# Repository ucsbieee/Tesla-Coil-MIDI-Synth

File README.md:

# UCSB IEEE Tesla Coil MIDI Synthesizer

This is the firmware and design files for a device to convert MIDI data to pulses to drive a Tesla coil. It enumerates as a USB MIDI device and can be sent live play data or a recorded MIDI file. It also enumerates as a USB audio device and can be sent PCM audio for greater control or for live instrument use.

The circuit board is based off of the [Arduino Due](https://docs.arduino.cc/hardware/due). It uses the similar SAM3A4C MCU, and has a fiber optic output for the big DRSSTC and a BNC port for the small Tesla Coil. It also has isolated physical MIDI in/out ports for connecting other instruments or daisy-chaining more MIDI interrupters. See [ucsbieee/ArduinoCore-SAM3A4C](https://github.com/ucsbieee/ArduinoCore-SAM3A4C) for an Arduino IDE board definition.

The device has six voices, which can each produce a single square wave tone at a variable duty cycle. They are ORed together to give a polyphonic effect.

## Uploading Firmware

New firmware can be uploaded using the Arduino IDE and the aforementioned [board definition](https://github.com/ucsbieee/ArduinoCore-SAM3A4C), or the [latest release](https://github.com/ucsbieee/Tesla-Coil-MIDI-Synth/releases/latest) (`.bin` file) can be uploaded using [BOSSA](https://github.com/shumatech/BOSSA) ([available from Homebrew](https://formulae.brew.sh/formula/bossa)).

### Arduino Library Dependencies
Available from the Arduino IDE library manager
 * [MIDIUSB](https://github.com/arduino-libraries/MIDIUSB)
 * [DueFlashStorage](https://github.com/sebnil/DueFlashStorage) (only if `SAVE_BASE_MIDI` is enabled, which it is not by default)

## Emulator

There is also an emulator that can be compiled to run on a normal computer so that songs can be developed without the physical hardware.

## MIDI Information

### MIDI Channels
 1. Clean (no effects)
 2. Effects
 3. Arpeggio and effects
 4. Drums

Standard MIDI pitch bend and aftertouch messages apply to all channels.

### Effects (CC number in parentheses)
 * Tremolo (rate = 102, depth = 92, delay = 103)
 * Vibrato (rate = 76, depth = 77, delay = 78)
 * ADSR (116, 117, 118, 119)
 * Arpeggio rate (14)

### Drum Samples
 * Kick (36/C2)
 * Snare (40/E2)
 * Clap (39/D#2)
 * Tom (48/C3)
 * Closed hi-hat (42/F#2)

### Physical MIDI Ports
All MIDI messages that come in over USB or the MIDI IN port are sent out the MIDI OUT port. Additionally, all messages that come in over the MIDI IN port are sent back to the computer over USB. This allows daisy-chaining multiple controllers using the physical MIDI ports, and allows recording any inputs from the physical MIDI IN port to the computer. Be careful not to create infinite MIDI loops in your DAW because of these behaviors.

## Audio Processing Modes
 * **Predictive**: Predict how much energy will be in a pulse based on the filtered derivative near zero crossing.
 * **Pulse Energy**: Output a pulse after a delay (~5ms) with width proportional to the area of the input pulse above the noise gate level. Pulse width clamped to maximum setting.
 * **Schmitt**: Output on when audio exceeds the noise gate level, then only turn off again once audio falls below negative noise gate level (Schmitt trigger behavior). Pulse width clamped to maximum setting.
 * **Clamped Binary**: Output on when audio exceeds the noise gate level. Pulse width clamped to maximum setting.
 * **Binary**: Output on when audio exceeds the noise gate level.
 * **Binary DDT**: Output on when the derivative of the audio exceeds a certain threshold. Pulse width clamped to maximum setting.
 * **Bin Oct Down**: Toggle output on rising edge. Input schmitt triggered. Output pulse width limited.
 * **PWM**: Output 48kHz PWM with pulse width proportional to the sample value. Audio baseline level subtracted away.
 * **PWM DDT**: Output 48kHz PWM with pulse width proportional to the derivative of the audio.

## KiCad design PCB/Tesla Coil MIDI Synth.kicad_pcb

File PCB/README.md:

# PCB

## Audio

We had the idea of using sampled audio output after the V2 boards were made. Unfortunately, the (unused) pins that have the necessary DMA capability are not broken out on the board. So, to get audio capability, you will need to solder a very thin wire (~34AWG) underneath the D10 pad on the microcontroller and run it to EXT_IN on the expansion header. Hope you're comfortable with BGA soldering :)

## Hacking
There are twelve extra pins on the board marked "Expansion," and they're there so you can add extra inputs or whatever you want to the board. Three are power (5V, 3.3V, GND), and seven go to digital/ADC pins on the MCU. The Arduino board definition is based off of the DUE, so take a look at the [DUE schematic](https://www.arduino.cc/en/uploads/Main/arduino-Due-schematic.pdf) or [variant.cpp](https://github.com/ucsbieee/ArduinoCore-SAM3A4C/blob/master/variants/arduino_due_x/variant.cpp) to see which Arduino pins they map to. These could be good for adding physical controls/music input of some kind.

There's also an input that is ORed with the voice signals before being sent to the outputs, and a 3.3V logic level copy of that combined output signal available. You can use these to make use of the output circuitry to control the Tesla coil with your own signals, combine voices from multiple interrupter boards (chaos), or whatever else you can think of.

## Erase and Reset Buttons
Pressing the "Erase" button on the PCB immediately deletes the firmware. Don't push it unless you intend to. This microcontroller has the SAM-BA bootloader included in ROM which is activated when the chip is blank, causing it to enumerate as a USB serial device and accept new firmware. If you ever get the board into a state where you can't program it, hit the erase button then reset and that should fix it. After uploading new firmware to a blank chip, you may need to re-power (instead of reset) the board. If it wasn't blank, you usually can just hit the reset button to make it run the new firmware.

If you accidentally nuked the chip, there's a firmware binary file in this repo and you can upload it using [bossa](https://github.com/shumatech/BOSSA/releases).

## If you want to make more

There should be a few extra unpopulated boards in the lab somewhere. See [BOM.csv](https://github.com/ucsbieee/Tesla-Coil-MIDI-Synth/blob/master/PCB/BOM.csv) for a list of parts you'll need. Parts without a DigiKey part number are generic stuff. Most resistors and caps are 0603, with a few 0805 (see footprint column).

You'll also likely want to use a solder paste stencil, especially for the BGA microcontroller. A file for the stencil is in the Gerber folder.

If you guys ever build a Tesla Coil symphony with a bunch of these things, please invite me back, I want to see :)

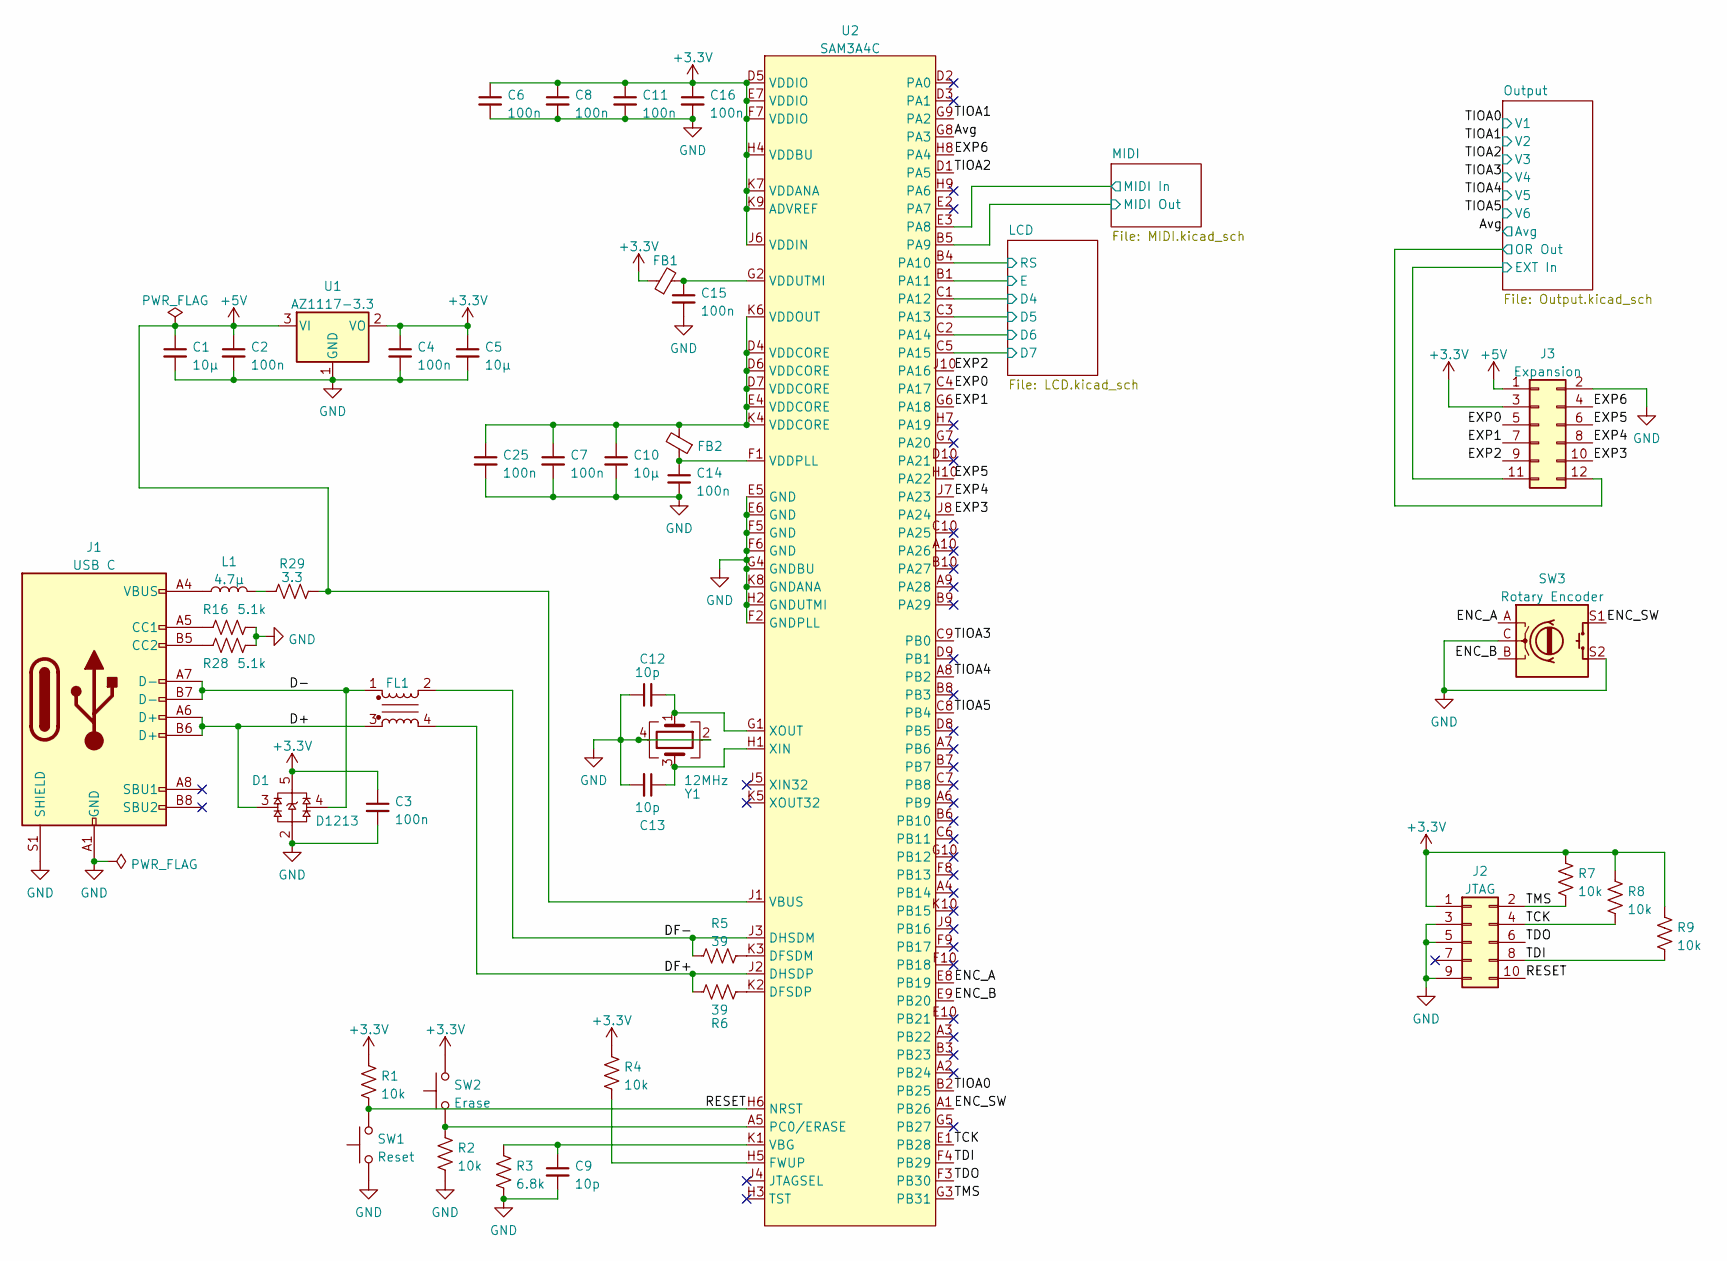
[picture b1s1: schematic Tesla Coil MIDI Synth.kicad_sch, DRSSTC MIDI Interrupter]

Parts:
C1, C5, C10: 10µ; C_0805_2012Metric_Pad1.18x1.45mm_HandSolder
C2, C3, C4, C6, C7, C8, C11, C14, C15, C16, C25: 100n; C_0603_1608Metric_Pad1.08x0.95mm_HandSolder
C9, C12, C13: 10p; C_0603_1608Metric_Pad1.08x0.95mm_HandSolder
D1: D1213; SOT25
FB1, FB2: FerriteBead_Small; L_0805_2012Metric_Pad1.05x1.20mm_HandSolder
FL1: Filter_EMI_CommonMode; Bourns_SRF2012AA
J1: USB C; GCT_USBC_USB4105
J2: JTAG; PinHeader_2x05_P1.27mm_Vertical
J3: Expansion; PinHeader_2x06_P2.54mm_Vertical
L1: 4.7µ; L_0805_2012Metric_Pad1.05x1.20mm_HandSolder
R1, R2, R4, R7, R8, R9: 10k; R_0603_1608Metric_Pad0.98x0.95mm_HandSolder
R3: 6.8k; R_0603_1608Metric_Pad0.98x0.95mm_HandSolder
R5, R6: 39; R_0603_1608Metric_Pad0.98x0.95mm_HandSolder
R16, R28: 5.1k; R_0603_1608Metric_Pad0.98x0.95mm_HandSolder
R29: 3.3; R_0603_1608Metric_Pad0.98x0.95mm_HandSolder
SW1: Reset; SW_PUSH_6mm
SW2: Erase; SW_PUSH_6mm
SW3: Rotary Encoder; Bourns_Encoder_PEC12R-4130F-S0012
U1: AZ1117-3.3; SOT-89-3
U2: SAM3A4C; TFBGA-100_9.0x9.0mm_Layout10x10_P0.8mm
Y1: 12MHz; Crystal_SMD_Abracon_ABM8G-4Pin_3.2x2.5mm

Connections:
+3.3V: C3.1, C4.1, C5.1, C6.1, C8.1, C11.1, C16.1, D1.5, FB1.1, J2.1, J3.3, R1.1, R4.1, R7.1, R8.1, R9.1, SW2.2, U1.2 (VO), U2.D5 (VDDIO), U2.E7 (VDDIO), U2.F7 (VDDIO), U2.H4 (VDDBU), U2.J6 (VDDIN), U2.K7 (VDDANA), U2.K9 (ADVREF); also elsewhere on the board
+5V: C1.1, C2.1, J3.1, R29.2, U1.3 (VI), U2.J1 (VBUS); also elsewhere on the board
/Avg: U2.G8 (PA3); also elsewhere on the board
/D+: D1.3, FL1.3, J1.A6 (D+), J1.B6 (D+)
/D-: D1.4, FL1.1, J1.A7 (D-), J1.B7 (D-)
/DF+: FL1.4, R6.1, U2.J2 (DHSDP)
/DF-: FL1.2, R5.1, U2.J3 (DHSDM)
/ENC_A: SW3.A, U2.E8 (PB19)
/ENC_B: SW3.B, U2.E9 (PB20)
/ENC_SW: SW3.S1, U2.A1 (PB26)
/EXP0: J3.5, U2.C4 (PA17)
/EXP1: J3.7, U2.G6 (PA18)
/EXP2: J3.9, U2.J10 (PA16)
/EXP3: J3.10, U2.J8 (PA24)
/EXP4: J3.8, U2.J7 (PA23)
/EXP5: J3.6, U2.H10 (PA22)
/EXP6: J3.4, U2.H8 (PA4)
/LCD/D4: U2.C1 (PA12); also elsewhere on the board
/LCD/D5: U2.C3 (PA13); also elsewhere on the board
/LCD/D6: U2.C2 (PA14); also elsewhere on the board
/LCD/D7: U2.C5 (PA15); also elsewhere on the board
/LCD/E: U2.B1 (PA11); also elsewhere on the board
/LCD/RS: U2.B4 (PA10); also elsewhere on the board
/MIDI/MIDI In: U2.E3 (PA8); also elsewhere on the board
/MIDI/MIDI Out: U2.B5 (PA9); also elsewhere on the board
/Output/EXT In: J3.11; also elsewhere on the board
/Output/OR Out: J3.12; also elsewhere on the board
/RESET: J2.10, R1.2, SW1.2, U2.H6 (NRST)
/TCK: J2.4, R8.2, U2.E1 (PB28)
/TDI: J2.8, R9.2, U2.F4 (PB29)
/TDO: J2.6, U2.F3 (PB30)
/TIOA0: U2.B2 (PB25); also elsewhere on the board
/TIOA1: U2.G9 (PA2); also elsewhere on the board
/TIOA2: U2.D1 (PA5); also elsewhere on the board
/TIOA3: U2.C9 (PB0); also elsewhere on the board
/TIOA4: U2.A8 (PB2); also elsewhere on the board
/TIOA5: U2.C8 (PB4); also elsewhere on the board
/TMS: J2.2, R7.2, U2.G3 (PB31)
GND: C1.2, C2.2, C3.2, C4.2, C5.2, C6.2, C7.2, C8.2, C9.2, C10.2, C11.2, C12.1, C13.2, C14.2, C15.2, C16.2, C25.2, D1.2, J1.A1 (GND), J1.A12 (GND), J1.B1 (GND), J1.B12 (GND), J1.S1 (SHIELD), J2.3, J2.5, J2.9, J3.2, R2.2, R3.2, R16.2, R28.2, SW1.1, SW3.C, SW3.S2, U1.1 (GND), U2.E5 (GND), U2.E6 (GND), U2.F2 (GNDPLL), U2.F5 (GND), U2.F6 (GND), U2.G4 (GNDBU), U2.H2 (GNDUTMI), U2.K8 (GNDANA), Y1.2, Y1.4; also elsewhere on the board
unnamed: J1.A5 (CC1), R16.1
unnamed: J1.B5 (CC2), R28.1
unnamed: J1.A4 (VBUS), J1.A9 (VBUS), J1.B4 (VBUS), J1.B9 (VBUS), L1.1
unnamed: L1.2, R29.1
unnamed: R5.2, U2.K3 (DFSDM)
unnamed: R6.2, U2.K2 (DFSDP)
unnamed: R4.2, U2.H5 (FWUP)
unnamed: R2.1, SW2.1, U2.A5 (PC0/ERASE)
unnamed: C9.1, R3.1, U2.K1 (VBG)
unnamed: C7.1, C10.1, C25.1, FB2.2, U2.D4 (VDDCORE), U2.D6 (VDDCORE), U2.D7 (VDDCORE), U2.E4 (VDDCORE), U2.K4 (VDDCORE), U2.K6 (VDDOUT)
unnamed: C14.1, FB2.1, U2.F1 (VDDPLL)
unnamed: C15.1, FB1.2, U2.G2 (VDDUTMI)
unnamed: C13.1, U2.H1 (XIN), Y1.3
unnamed: C12.2, U2.G1 (XOUT), Y1.1

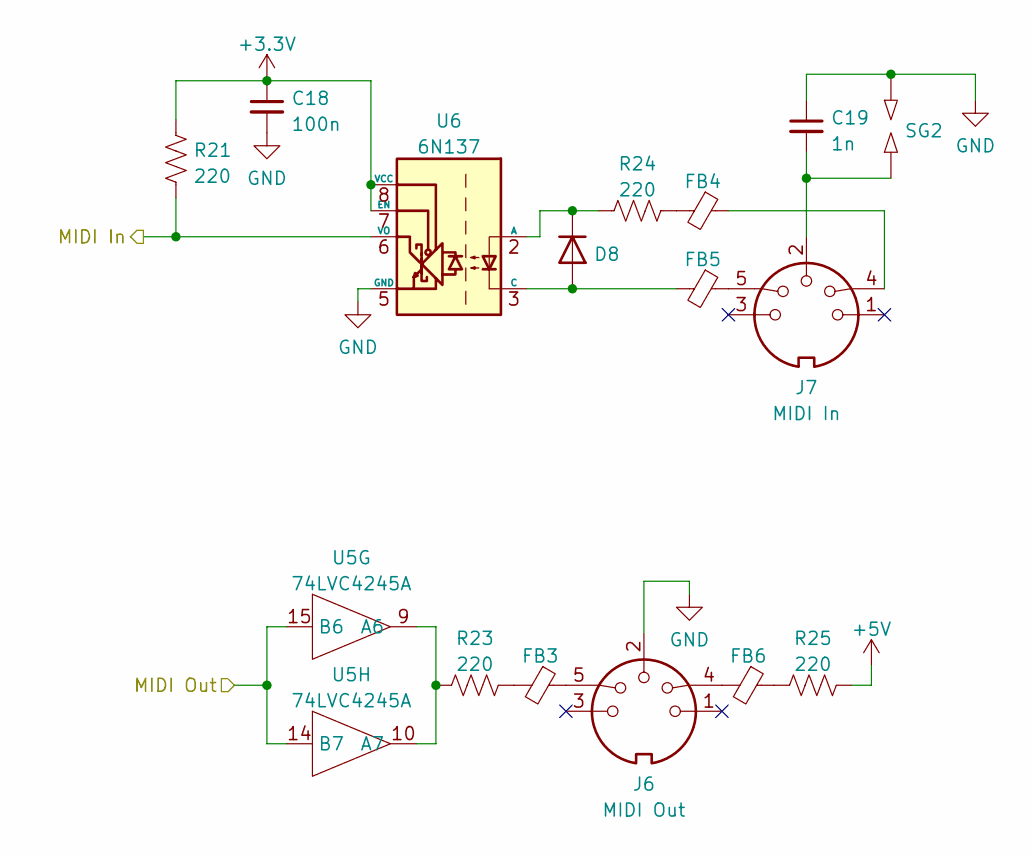
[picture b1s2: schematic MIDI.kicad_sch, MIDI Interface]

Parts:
C18: 100n; C_0603_1608Metric_Pad1.08x0.95mm_HandSolder
C19: 1n; C_Disc_D7.5mm_W5.0mm_P7.50mm
D8: D; D_SOD-123
FB3, FB4, FB5, FB6: FerriteBead_Small; L_0805_2012Metric_Pad1.05x1.20mm_HandSolder
J6: MIDI Out; CUI_DIN_SDS-50J
J7: MIDI In; CUI_DIN_SDS-50J
R21, R23, R24, R25: 220; R_0603_1608Metric_Pad0.98x0.95mm_HandSolder
SG2: SparkGap; Spark_Gap
U5: 74LVC4245A; TSSOP-24_4.4x7.8mm_P0.65mm
U6: 6N137; DIP-8_W7.62mm

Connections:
+3.3V: C18.1, R21.1, U6.7 (EN), U6.8 (VCC); also elsewhere on the board
+5V: R25.2; also elsewhere on the board
/MIDI/MIDI In: R21.2, U6.6 (VO); also elsewhere on the board
/MIDI/MIDI Out: U5.14 (B7), U5.15 (B6); also elsewhere on the board
GND: C18.2, C19.1, J6.2, SG2.2, U6.5 (GND); also elsewhere on the board
unnamed: C19.2, J7.2, SG2.1
unnamed: D8.2 (A), FB5.2, U6.3 (C)
unnamed: D8.1 (K), R24.1, U6.2 (A)
unnamed: FB3.1, J6.5
unnamed: FB3.2, R23.2
unnamed: FB4.1, J7.4
unnamed: FB4.2, R24.2
unnamed: FB5.1, J7.5
unnamed: FB6.1, R25.1
unnamed: FB6.2, J6.4
unnamed: R23.1, U5.9 (A6), U5.10 (A7)

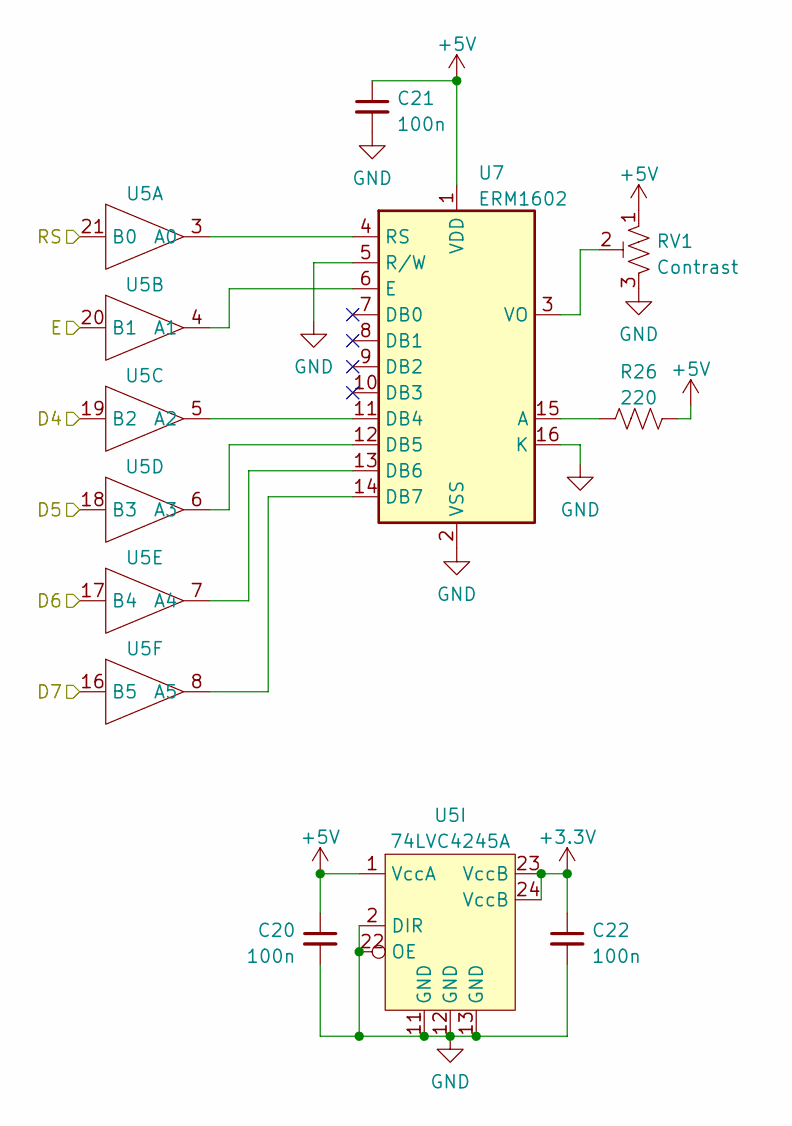
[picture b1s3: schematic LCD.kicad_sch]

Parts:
C20, C21, C22: 100n; C_0603_1608Metric_Pad1.08x0.95mm_HandSolder
R26: 220; R_0603_1608Metric_Pad0.98x0.95mm_HandSolder
RV1: Contrast; Potentiometer_Bourns_TC33X_Vertical
U5: 74LVC4245A; TSSOP-24_4.4x7.8mm_P0.65mm
U7: ERM1602

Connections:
+3.3V: C22.1, U5.23 (VccB), U5.24 (VccB); also elsewhere on the board
+5V: C20.1, C21.1, R26.2, RV1.1, U5.1 (VccA), U7.1 (VDD); also elsewhere on the board
/LCD/D4: U5.19 (B2); also elsewhere on the board
/LCD/D5: U5.18 (B3); also elsewhere on the board
/LCD/D6: U5.17 (B4); also elsewhere on the board
/LCD/D7: U5.16 (B5); also elsewhere on the board
/LCD/E: U5.20 (B1); also elsewhere on the board
/LCD/RS: U5.21 (B0); also elsewhere on the board
GND: C20.2, C21.2, C22.2, RV1.3, U5.2 (DIR), U5.11 (GND), U5.12 (GND), U5.13 (GND), U5.22 (OE), U7.2 (VSS), U7.5 (R/W), U7.16 (K); also elsewhere on the board
unnamed: U5.3 (A0), U7.4 (RS)
unnamed: U5.4 (A1), U7.6 (E)
unnamed: U5.5 (A2), U7.11 (DB4)
unnamed: U5.6 (A3), U7.12 (DB5)
unnamed: U5.7 (A4), U7.13 (DB6)
unnamed: U5.8 (A5), U7.14 (DB7)
unnamed: R26.1, U7.15 (A)
unnamed: RV1.2, U7.3 (VO)

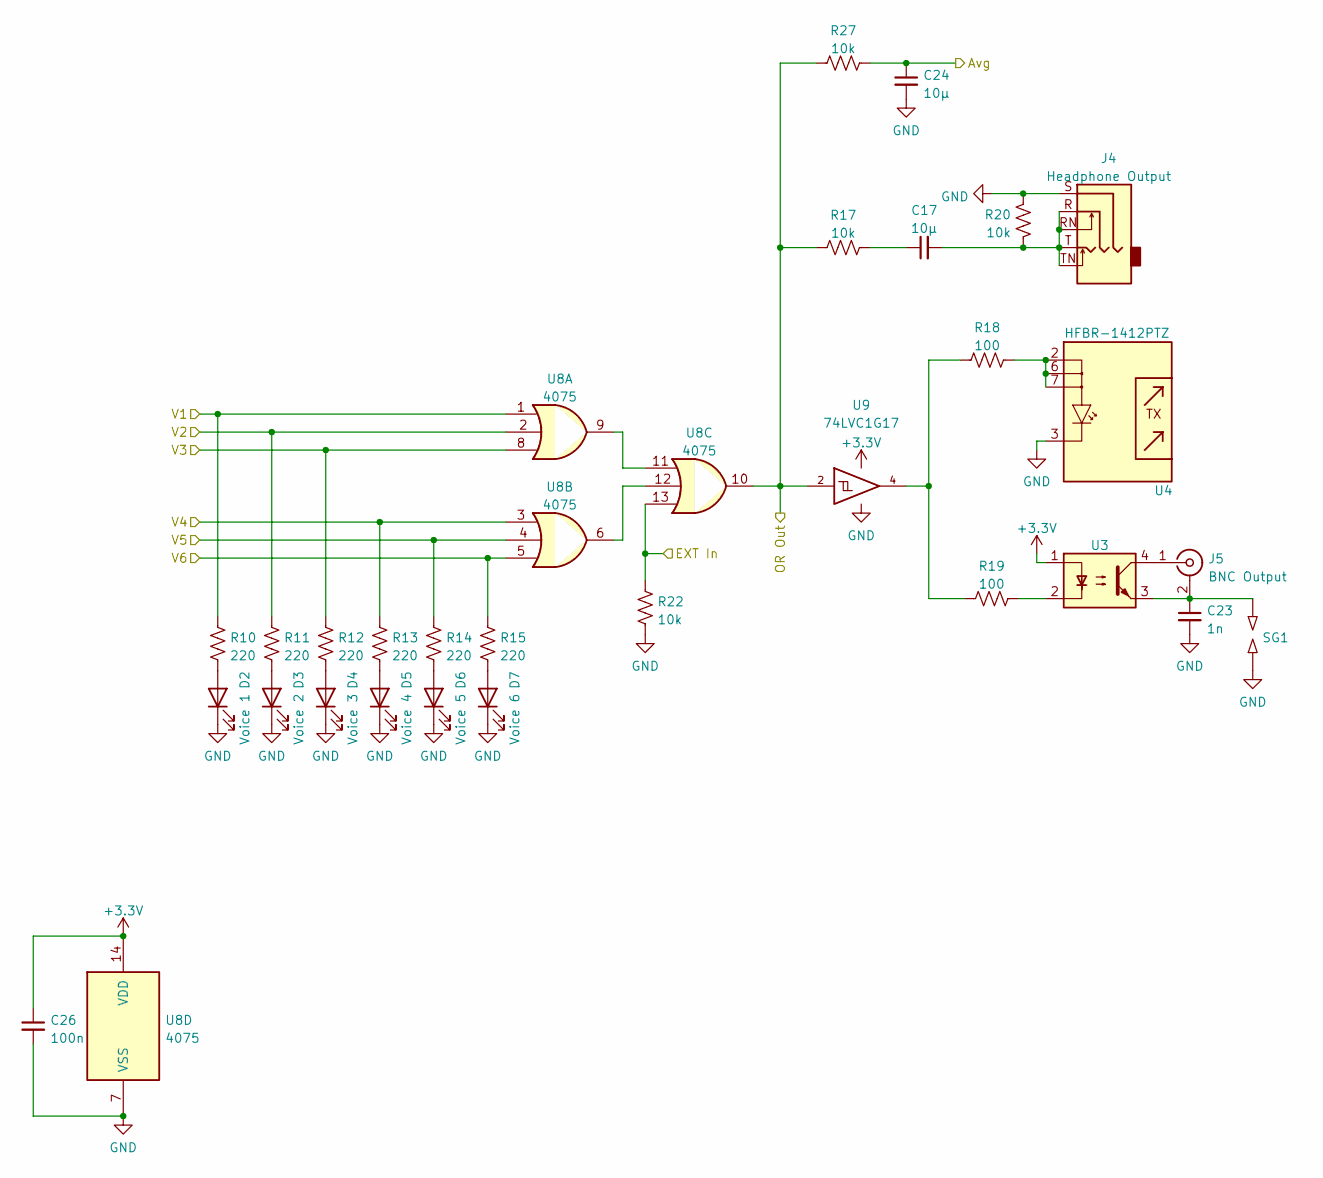
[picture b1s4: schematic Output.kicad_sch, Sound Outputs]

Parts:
C17, C24: 10µ; C_0805_2012Metric_Pad1.18x1.45mm_HandSolder
C23: 1n; C_Disc_D7.5mm_W5.0mm_P7.50mm
C26: 100n; C_0603_1608Metric_Pad1.08x0.95mm_HandSolder
D2: Voice 1; LED_D5.0mm
D3: Voice 2; LED_D5.0mm
D4: Voice 3; LED_D5.0mm
D5: Voice 4; LED_D5.0mm
D6: Voice 5; LED_D5.0mm
D7: Voice 6; LED_D5.0mm
J4: Headphone Output; Adam_Tech_ASJ-99H-X-HT-TR
J5: BNC Output; Adam_Tech_BNC_RF1-01K-D-00-50-BK-HDW
R10, R11, R12, R13, R14, R15: 220; R_0603_1608Metric_Pad0.98x0.95mm_HandSolder
R17, R20, R22, R27: 10k; R_0603_1608Metric_Pad0.98x0.95mm_HandSolder
R18, R19: 100; R_0603_1608Metric_Pad0.98x0.95mm_HandSolder
SG1: SparkGap; Spark_Gap
U3: SFH617A-1; DIP-4_W10.16mm
U4: HFBR-1412PTZ; Broadcom_HFBR-1412PTZ
U8: 4075; SOIC-14_3.9x8.7mm_P1.27mm
U9: 74LVC1G17; SOT-23-5

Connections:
+3.3V: C26.1, U3.1, U8.14 (VDD), U9.5 (VCC); also elsewhere on the board
/Avg: C24.1, R27.2; also elsewhere on the board
/Output/EXT In: R22.1, U8.13; also elsewhere on the board
/Output/OR Out: R17.1, R27.1, U8.10, U9.2; also elsewhere on the board
/TIOA0: R10.1, U8.1; also elsewhere on the board
/TIOA1: R11.1, U8.2; also elsewhere on the board
/TIOA2: R12.1, U8.8; also elsewhere on the board
/TIOA3: R13.1, U8.3; also elsewhere on the board
/TIOA4: R14.1, U8.4; also elsewhere on the board
/TIOA5: R15.1, U8.5; also elsewhere on the board
GND: C23.2, C24.2, C26.2, D2.1 (K), D3.1 (K), D4.1 (K), D5.1 (K), D6.1 (K), D7.1 (K), J4.S, R20.1, R22.2, SG1.1, U4.3, U8.7 (VSS), U9.3 (GND); also elsewhere on the board
unnamed: C17.1, R17.2
unnamed: C17.2, J4.R, J4.RN, J4.T, J4.TN, R20.2
unnamed: D2.2 (A), R10.2
unnamed: D3.2 (A), R11.2
unnamed: D4.2 (A), R12.2
unnamed: D5.2 (A), R13.2
unnamed: D6.2 (A), R14.2
unnamed: D7.2 (A), R15.2
unnamed: C23.1, J5.2 (Ext), SG1.2, U3.3
unnamed: J5.1 (In), U3.4
unnamed: R18.1, U4.2, U4.6, U4.7
unnamed: R18.2, R19.2, U9.4
unnamed: R19.1, U3.2
unnamed: U8.9, U8.11
unnamed: U8.6, U8.12

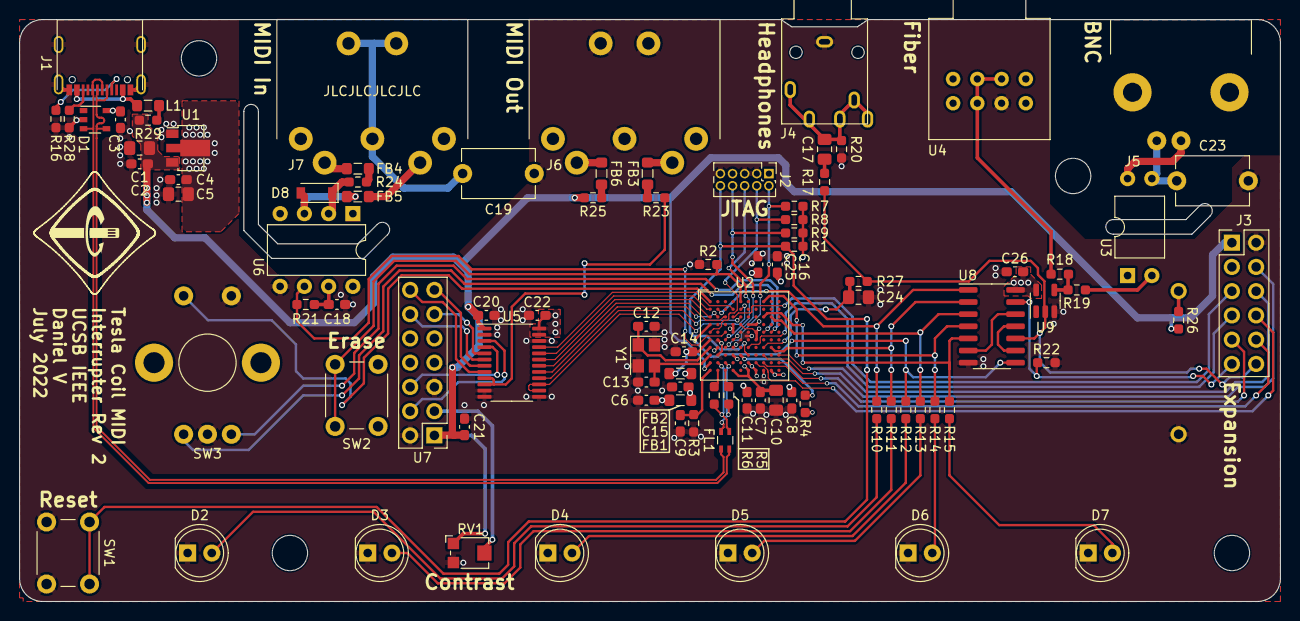
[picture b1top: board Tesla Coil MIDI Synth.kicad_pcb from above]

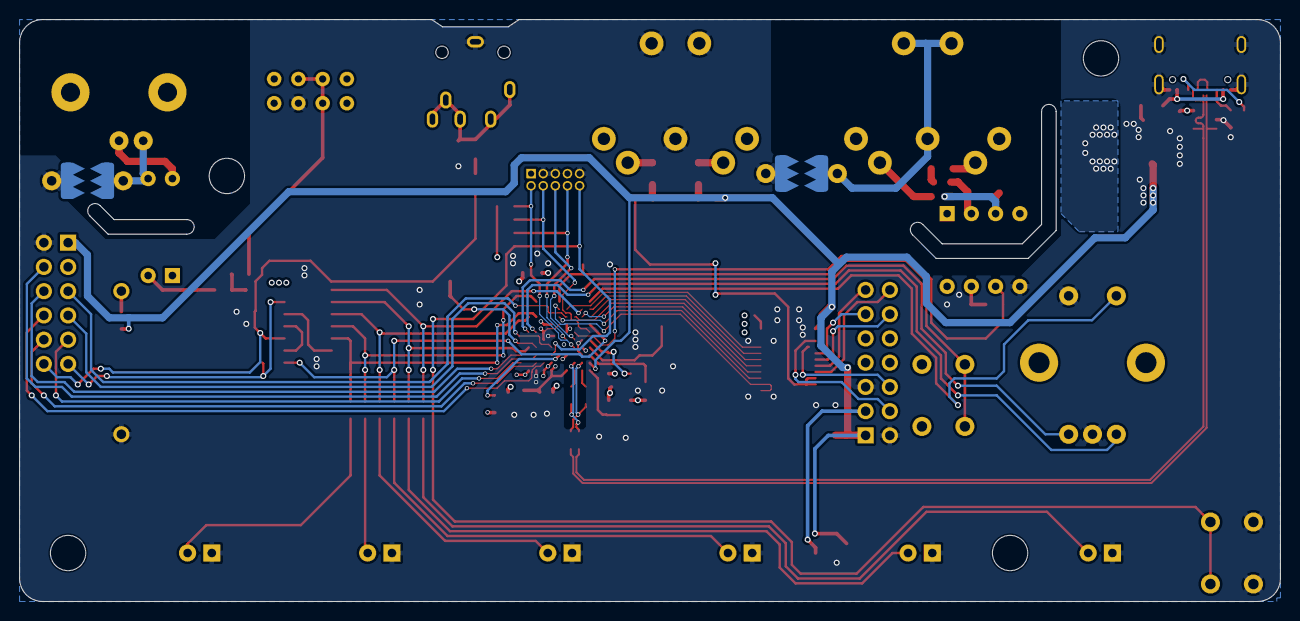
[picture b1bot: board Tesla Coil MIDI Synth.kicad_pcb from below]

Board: 4 copper layers, 132.1 x 61.0 mm, 94 parts (2 on the bottom side), 87 nets.

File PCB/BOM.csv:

Item,Qty,Reference(s),Value,LibPart,Footprint,Datasheet,DigiKey Part Number
1,5,"C1, C5, C10, C17, C24",10µ,Device:C_Small,Capacitor_SMD:C_0805_2012Metric_Pad1.18x1.45mm_HandSolder,,
2,16,"C2, C3, C4, C6, C7, C8, C11, C14, C15, C16, C18, C20, C21, C22, C25, C26",100n,Device:C_Small,Capacitor_SMD:C_0603_1608Metric_Pad1.08x0.95mm_HandSolder,,
3,3,"C9, C12, C13",10p,Device:C_Small,Capacitor_SMD:C_0603_1608Metric_Pad1.08x0.95mm_HandSolder,,
4,2,"C19, C23",1n,Device:C_Small,Capacitor_THT:C_Disc_D7.5mm_W5.0mm_P7.50mm,,
5,1,D1,D1213,Custom_Symbols:D1213,Custom_Footprints:SOT25,https://www.diodes.com/assets/Datasheets/D1213A-02SM.pdf,D1213A-02SM-7DICT-ND
6,1,D2,Voice 1,Device:LED,LED_THT:LED_D5.0mm,,
7,1,D3,Voice 2,Device:LED,LED_THT:LED_D5.0mm,,
8,1,D4,Voice 3,Device:LED,LED_THT:LED_D5.0mm,,
9,1,D5,Voice 4,Device:LED,LED_THT:LED_D5.0mm,,
10,1,D6,Voice 5,Device:LED,LED_THT:LED_D5.0mm,,
11,1,D7,Voice 6,Device:LED,LED_THT:LED_D5.0mm,,
12,1,D8,D,Device:D,Diode_SMD:D_SOD-123,,1727-7320-1-ND
13,6,"FB1, FB2, FB3, FB4, FB5, FB6",FerriteBead_Small,Device:FerriteBead_Small,Inductor_SMD:L_0805_2012Metric_Pad1.05x1.20mm_HandSolder,,1276-6377-1-ND
14,1,FL1,Filter_EMI_CommonMode,Device:Filter_EMI_CommonMode,Custom_Footprints:Bourns_SRF2012AA,,SRF2012A-900YACT-ND
15,1,J1,USB C,Connector:USB_C_Receptacle_USB2.0,Custom_Footprints:GCT_USBC_USB4105,,2073-USB4105-GF-ACT-ND
16,1,J2,JTAG,Connector_Generic:Conn_02x05_Odd_Even,Connector_PinHeader_1.27mm:PinHeader_2x05_P1.27mm_Vertical,,
17,1,J3,Expansion,Connector_Generic:Conn_02x05_Odd_Even,Connector_PinHeader_2.54mm:PinHeader_2x05_P2.54mm_Vertical,,
18,1,J4,Headphone Output,Connector:AudioJack3_SwitchTR,Custom_Footprints:Adam_Tech_ASJ-99H-X-HT-TR,,2057-ASJ-99H-R-HT-T/RCT-ND
19,1,J5,BNC Output,Connector:Conn_Coaxial,Custom_Footprints:Adam_Tech_BNC_RF1-01K-D-00-50-BK-HDW,,"2057-RF1-01K-D-00-50-BK-HDW-ND, SC2808-ND"
20,1,J6,MIDI Out,Connector:DIN-5_180degree,Custom_Footprints:CUI_DIN_SDS-50J,,CP-2350-ND
21,1,J7,MIDI In,Connector:DIN-5_180degree,Custom_Footprints:CUI_DIN_SDS-50J,,CP-2350-ND
22,1,L1,4.7µ,Device:L,Inductor_SMD:L_0805_2012Metric_Pad1.05x1.20mm_HandSolder,,445-8659-1-ND
23,10,"R1, R2, R4, R7, R8, R9, R17, R20, R22, R27",10k,Device:R_US,Resistor_SMD:R_0603_1608Metric_Pad0.98x0.95mm_HandSolder,,
24,1,R3,6.8k,Device:R_US,Resistor_SMD:R_0603_1608Metric_Pad0.98x0.95mm_HandSolder,,
25,2,"R5, R6",39,Device:R_US,Resistor_SMD:R_0603_1608Metric_Pad0.98x0.95mm_HandSolder,,
26,11,"R10, R11, R12, R13, R14, R15, R21, R23, R24, R25, R26",220,Device:R_US,Resistor_SMD:R_0603_1608Metric_Pad0.98x0.95mm_HandSolder,,
27,2,"R16, R28",5.1k,Device:R_US,Resistor_SMD:R_0603_1608Metric_Pad0.98x0.95mm_HandSolder,,
28,2,"R18, R19",100,Device:R_US,Resistor_SMD:R_0603_1608Metric_Pad0.98x0.95mm_HandSolder,,
29,1,R29,3.3,Device:R_US,Resistor_SMD:R_0603_1608Metric_Pad0.98x0.95mm_HandSolder,,
30,1,RV1,Contrast,Device:R_Potentiometer_Trim_US,Potentiometer_SMD:Potentiometer_Bourns_TC33X_Vertical,,TC33X-103ECT-ND
31,2,"SG1, SG2",SparkGap,Device:SparkGap,Custom_Footprints:Spark_Gap,,
32,1,SW1,Reset,Switch:SW_Push,Button_Switch_THT:SW_PUSH_6mm,,
33,1,SW2,Erase,Switch:SW_Push,Button_Switch_THT:SW_PUSH_6mm,,
34,1,SW3,Rotary Encoder,Device:RotaryEncoder_Switch,Custom_Footprints:Bourns_Encoder_PEC12R-4130F-S0012,,"PEC12R-4130F-S0012-ND, 1568-1601-ND"
35,1,U1,AZ1117-3.3,Regulator_Linear:AZ1117-3.3,Package_TO_SOT_SMD:SOT-89-3,,AZ1117CR-3.3TRG1DICT-ND
36,1,U2,SAM3A4C,Custom_Symbols:SAM3A4C,Package_BGA:TFBGA-100_9.0x9.0mm_Layout10x10_P0.8mm,http://www.microchip.com/mymicrochip/filehandler.aspx?ddocna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,1611-ATSAM3A4CA-CU-ND
37,1,U3,SFH617A-1,Isolator:SFH617A-1,Package_DIP:DIP-4_W10.16mm,,732-140817141310-ND
38,1,U4,HFBR-1412PTZ,Custom_Symbols:HFBR-1412PTZ,Custom_Footprints:Broadcom_HFBR-1412PTZ,https://docs.broadcom.com/doc/AV02-0176EN,516-4074-ND
39,1,U5,74LVC4245A,Custom_Symbols:74LVC4245A,Package_SO:TSSOP-24_4.4x7.8mm_P0.65mm,https://assets.nexperia.com/documents/data-sheet/74LVC4245A.pdf,1727-4308-1-ND
40,1,U6,6N137,Isolator:6N137,Package_DIP:DIP-8_W7.62mm,,160-1791-ND
41,1,U7,ERM1602,Custom_Symbols:ERM1602,Custom_Footprints:ERM1602,https://www.buydisplay.com/download/manual/ERM1602-2.1_Serie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,
42,1,U8,4075,4xxx:4075,Package_SO:SOIC-14_3.9x8.7mm_P1.27mm,,296-SN74HCS4075DRCT-ND
43,1,U9,74LVC1G17,74xGxx:74LVC1G17,Package_TO_SOT_SMD:SOT-23-5,,296-11933-1-ND
44,1,Y1,12MHz,Device:Crystal_GND24,Crystal:Crystal_SMD_Abracon_ABM8G-4Pin_3.2x2.5mm,,535-10901-1-ND

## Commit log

2022-04-21 MIDI is cool
2022-05-04 reworked arpeggio code to allow it to carry through ADSR release
    so many timer race condition bugs
    for loops are hard
    why
    why
    why
    why
2022-05-04 actually DO need to update the timers even if the stuff didn't change
2022-05-04 improved drum samples
2022-05-10 added physical MIDI support
2022-05-10 made pulse width control more intelligent
    pulse width is now controlled as duty cycle rather than as a
    percentage of the max width
    added compile-time option to automatically reduce all pulse widths
    proportional to how much stuff is playing at once
2022-05-20 added volume control
2022-05-20 made MIDI velocity optionally control absolute pulse width or relative to frequency
2022-05-21 small fixes
2022-08-08 designed PCB
2022-08-16 interactive BOM
2022-08-17 refactored code and added UI for new PCB
2022-08-17 hide ibom.html from linguist
2022-08-19 fix board thickness
2022-08-19 notes on PCB
2022-08-19 note on erase button
2022-08-19 update BOM
2022-08-19 add case files
2022-08-19 fix MIDI note velocity on effects channels
2022-08-19 improved MIDI channel display
2022-08-19 correct README
2022-08-20 adjusted display of speeds
2022-08-26 small LCD bug
2022-12-22 fixed PCB
    * Added 5.1k resistors to CC lines on USB-C port
    * Replaced diode OR thing and MOSFET with too low of a threshold voltage with a real OR gate and buffer
    * Fixed polarity of BNC output
    * Made headphone output not murderously loud and asymmetric
    * Added direct in/out to expansion pins
    * Reduced impedance into ADC for average volume level sensing
2023-01-16 made pitch bend and vibrato more musical
    should relate to powers of 2 instead of being linear
2023-04-03 change pitch bend range to 2 semitones
2023-04-03 sustain pedal controls release parameter
2023-04-13 improved power line filtering
2023-04-29 changed via size to 0.3mm drill
2023-05-20 adjust value to make LCD happy
2023-05-21 make case curvy and update PCB model
2023-07-22 wrote emulator
2023-07-22 make timer behavior more realistic
    also fixes pitch bend and vibrato weirdness
2023-07-22 improved audio generation
2023-07-23 statically-linked macOS universal binary build
2023-07-23 fix build on Linux
2023-07-23 GCC please stop
2023-07-23 change submoudle to use HTTPS
2023-07-23 Windows build
2024-02-23 add USB disconnect failsafe
2024-04-10 address compiler warnings
2024-04-10 remove unmaintained DUE version
2024-04-10 add picture
2024-04-14 add note on uploading firmware
2024-04-14 add CI
2024-04-21 adjust CI
2024-04-21 move variable defs out of headers
2024-04-21 add FW version boot screen
2024-04-22 add new AudioEngine system
2024-04-22 emulator version message
2024-04-23 switch to `#pragma once`
2024-04-28 mention required Arduino libraries
2024-04-28 improve emulator audio realism
    convolve output with sampled IR of Tesla Coil + reverb
2024-05-04 optimize divisions
2024-05-04 run audio processing in callback
    separate generator thread was not running with high enough priority and was causing dropouts
2024-05-04 experimental USB audio support
    requires hardware modification to rev <= 2 boards to connect PWM output pin
2024-05-04 add emulation of screen
2024-09-30 move DMA ISR
2024-11-10 refactor into classes
2024-11-10 added audio processing modes
2024-11-11 move parameter updates out of interrupt handler
    to solve crash due to interrupt overload
2024-11-12 handle channel aftertouch messages
    corrected interpretation of length of messages on physical port
    also added physical MIDI IN -> USB passthrough
2024-11-12 fix encoder bug
2024-11-12 add schmitt trigger audio mode
2024-11-13 added binary octave down audio mode
2024-11-19 change binary DDT mode threshold
2025-05-23 disable emulator CI build
    SDL dependency hell makes static build annoying
2025-05-23 upgrade AudioModeBinaryOctave
    added schmitt trigger and pulse width limit, fixed name length
2025-05-23 remove space from FQBN
2025-05-23 v2.0
